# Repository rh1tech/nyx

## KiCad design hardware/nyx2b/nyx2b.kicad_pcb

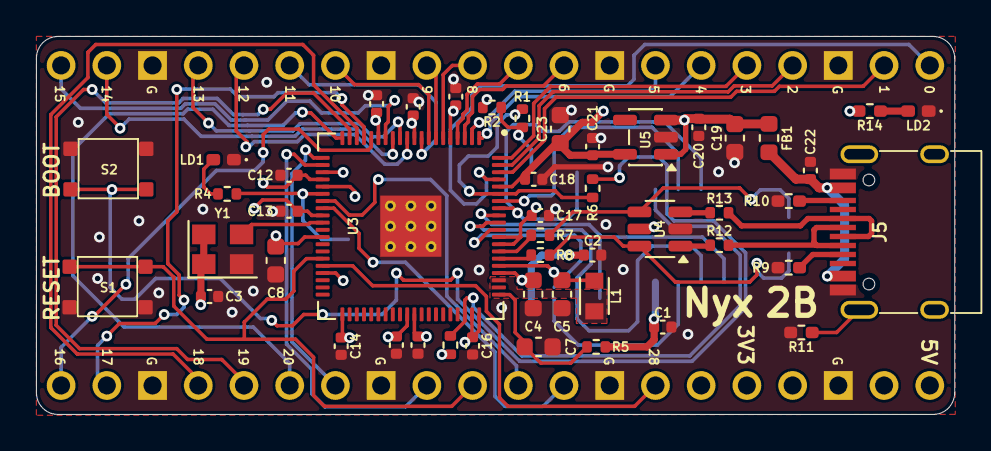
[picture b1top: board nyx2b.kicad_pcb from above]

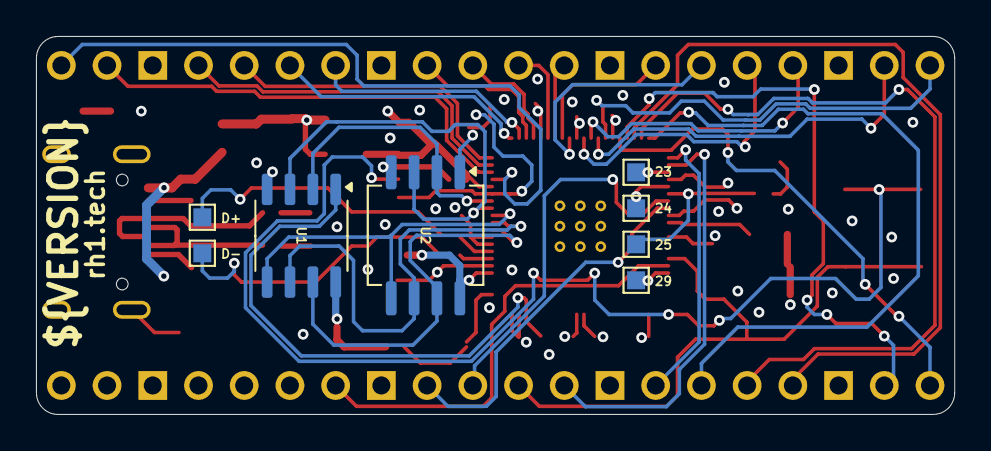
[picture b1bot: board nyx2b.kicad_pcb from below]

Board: 4 copper layers, 51.0 x 21.0 mm, 54 parts (4 on the bottom side), 61 nets.

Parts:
C1, C2, C3, C6, C9, C10, C11, C12, C13, C14, C15, C16, C17, C18, C20, C21, C22: 100n; Capacitor (0402, S)
C4, C5, C7, C8: 4.7u; Capacitor (0603, S)
C19, C23: 10u; Capacitor (0603, S)
FB1: 330R; L_0603_1608Metric
J1: CON_PICO_21-40
J2: CON_PICO_1-20
J3: Test Points (1mm x 5)
J4: Test Points (1mm x 2)
J5: USB4215-03-A; USB Type C
L1: 3.3u; IND_LQH2MCN100K02L
LD1: Blue; LED (0402)
LD2: Green; LED (0402)
R1: 0R; Resistor (0402, S)
R2, R3: 10K; Resistor (0402, S)
R4, R6: 1K; Resistor (0402, S)
R5: 33; Resistor (0402, S)
R7, R8: 27; Resistor (0402, S)
R9, R10: 5.1K; Resistor (0402)
R11: 1M; Resistor (0402)
R12, R13: 22R; Resistor (0402, S)
R14: 1K; Resistor (0402)
S1: Reset; Button (SMD, 3x3mm, 1-1)
S2: Boot; Button (SMD, 3x3mm, 1-1)
U1: ESP-PSRAM32; SO-8
U2: W25Q128JVS; SOIC-8
U3: RP2350_80QFN; RP2350-QFN-80-1EP_10x10_P0.4mm_EP3.4x3.4mm_ThermalVias
U4: USBLC6-2SC6; SOT-23-6
U5: ME6211C33M5; SOT-23-5
Y1: ASE-12MHz; Crystal (3225, active)

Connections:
+1V1: C5.1, C6.1, C8.1, C9.1, L1.1, U3.10 (DVDD), U3.32 (DVDD), U3.51 (DVDD), U3.65 (VREG_FB)
+3V3: C1.1, C2.1, C3.1, C4.1, C10.1, C11.1, C12.1, C13.1, C14.1, C15.1, C16.1, C17.1, C18.1, C21.1, C23.1, J1.36, R2.1, R3.2, R5.1, R14.2, U1.8 (VCC), U2.8 (VCC), U3.5 (IOVDD), U3.15 (IOVDD), U3.24 (IOVDD), U3.29 (IOVDD), U3.41 (IOVDD), U3.50 (IOVDD), U3.59 (ADC_AVDD), U3.60 (IOVDD), U3.64 (VREG_VIN), U3.68 (USB_OTP_VDD), U3.69 (QSPI_IOVDD), U3.76 (IOVDD), U5.5 (V_{OUT}), Y1.1 (EN), Y1.4 (Vdd)
/D+: J4.1, R7.1, U4.4 (I/O2)
/D-: J4.2, R8.1, U4.6 (I/O1)
/GPIO0: J2.1, U3.77 (GPIO0)
/GPIO1: J2.2, U3.78 (GPIO1)
/GPIO2: J2.4, U3.79 (GPIO2)
/GPIO3: J2.5, U3.80 (GPIO3)
/GPIO4: J2.6, U3.1 (GPIO4)
/GPIO5: J2.7, U3.2 (GPIO5)
/GPIO6: J2.9, U3.3 (GPIO6)
/GPIO7: J2.10, U3.4 (GPIO7)
/GPIO8: J2.11, U3.6 (GPIO8)
/GPIO9: J2.12, U3.7 (GPIO9)
/GPIO10: J2.14, U3.8 (GPIO10)
/GPIO11: J2.15, U3.9 (GPIO11)
/GPIO12: J2.16, U3.11 (GPIO12)
/GPIO13: J2.17, U3.12 (GPIO13)
/GPIO14: J2.19, U3.13 (GPIO14)
/GPIO15: J2.20, U3.14 (GPIO15)
/GPIO16: J1.21, U3.16 (GPIO16)
/GPIO17: J1.22, U3.17 (GPIO17)
/GPIO18: J1.24, U3.18 (GPIO18)
/GPIO19: J1.25, U3.19 (GPIO19)
/GPIO20: J1.26, U3.20 (GPIO20)
/GPIO21: J1.27, U3.21 (GPIO21)
/GPIO22: J1.29, U3.22 (GPIO22)
/GPIO23: J3.1, U3.23 (GPIO23)
/GPIO24: J3.2, U3.25 (GPIO24)
/GPIO26: J1.31, U3.27 (GPIO26)
/GPIO27: J1.32, U3.28 (GPIO27)
/GPIO28: J1.34, U3.36 (GPIO28)
/GPIO29: J3.4, U3.37 (GPIO29)
/GPIO47: R3.1, U1.1 (~CE), U3.58 (GPIO47_ADC7)
/Power/VBUS_IN: C22.1, FB1.2, J5.2 (VBUS), J5.11 (VBUS)
/RP2350B/FLASH_SS: R1.2, R2.2, U2.1 (~CS)
/RP2350B/QSPI_SCLK: U1.6 (SCLK), U2.6 (CLK), U3.71 (QSPI_SCLK)
/RP2350B/QSPI_SD0: U1.5 (SI/SIO), U2.5 (DI(IO0)), U3.72 (QSPI_SD0)
/RP2350B/QSPI_SD1: U1.2 (SO/SIO), U2.2 (DO(IO1)), U3.74 (QSPI_SD1)
/RP2350B/QSPI_SD2: U1.3 (SIO2), U2.3 (IO2), U3.73 (QSPI_SD2)
/RP2350B/QSPI_SD3: U1.7 (SIO3), U2.7 (IO3), U3.70 (QSPI_SD3)
/RP2350B/QSPI_SS: R1.1, R6.1, U3.75 (QSPI_SS)
/RP2350B/VREG_AVDD: C7.1, R5.2, U3.61 (VREG_AVDD)
/RP2350B/VREG_LX: L1.2, U3.63 (VREG_LX)
/RP2350B/XIN: U3.30 (XIN), Y1.3 (OUT)
/RP2350B/~USB_BOOT: R6.2, S2.2
/RUN: J1.30, S1.1, U3.35 (RUN)
GND: C1.2, C2.2, C3.2, C4.2, C5.2, C6.2, C7.2, C8.2, C9.2, C10.2, C11.2, C12.2, C13.2, C14.2, C15.2, C16.2, C17.2, C18.2, C19.1, C20.1, C21.2, C22.2, C23.2, J1.23, J1.28, J1.33, J1.38, J2.3, J2.8, J2.13, J2.18, J5.1 (GND), J5.12 (GND), LD1.1 (K), LD2.1 (K), R9.1, R10.1, R11.2, S1.2, S2.1, U1.4 (VSS), U2.4 (GND), U3.62 (VREG_PGND), U3.81 (GND), U4.2 (GND), U5.2 (V_{SS}), Y1.2 (GND)
GPIO25: J3.3, R4.2, U3.26 (GPIO25)
unnamed: J5.4 (CC1), R9.2
unnamed: J5.10 (CC2), R10.2
unnamed: J5.5 (DN2), J5.7 (DN1), R12.2
unnamed: J5.6 (DP1), J5.8 (DP2), R13.2
unnamed: J5.13 (SHIELD), R11.1
unnamed: LD1.2 (A), R4.1
unnamed: LD2.2 (A), R14.1
unnamed: R12.1, U4.1 (I/O1)
unnamed: R13.1, U4.3 (I/O2)
unnamed: R8.2, U3.66 (USB_DM)
unnamed: R7.2, U3.67 (USB_DP)
VBUS: C19.2, C20.2, FB1.1, J1.40, U4.5 (VBUS), U5.1 (V_{IN}), U5.3 (CE)

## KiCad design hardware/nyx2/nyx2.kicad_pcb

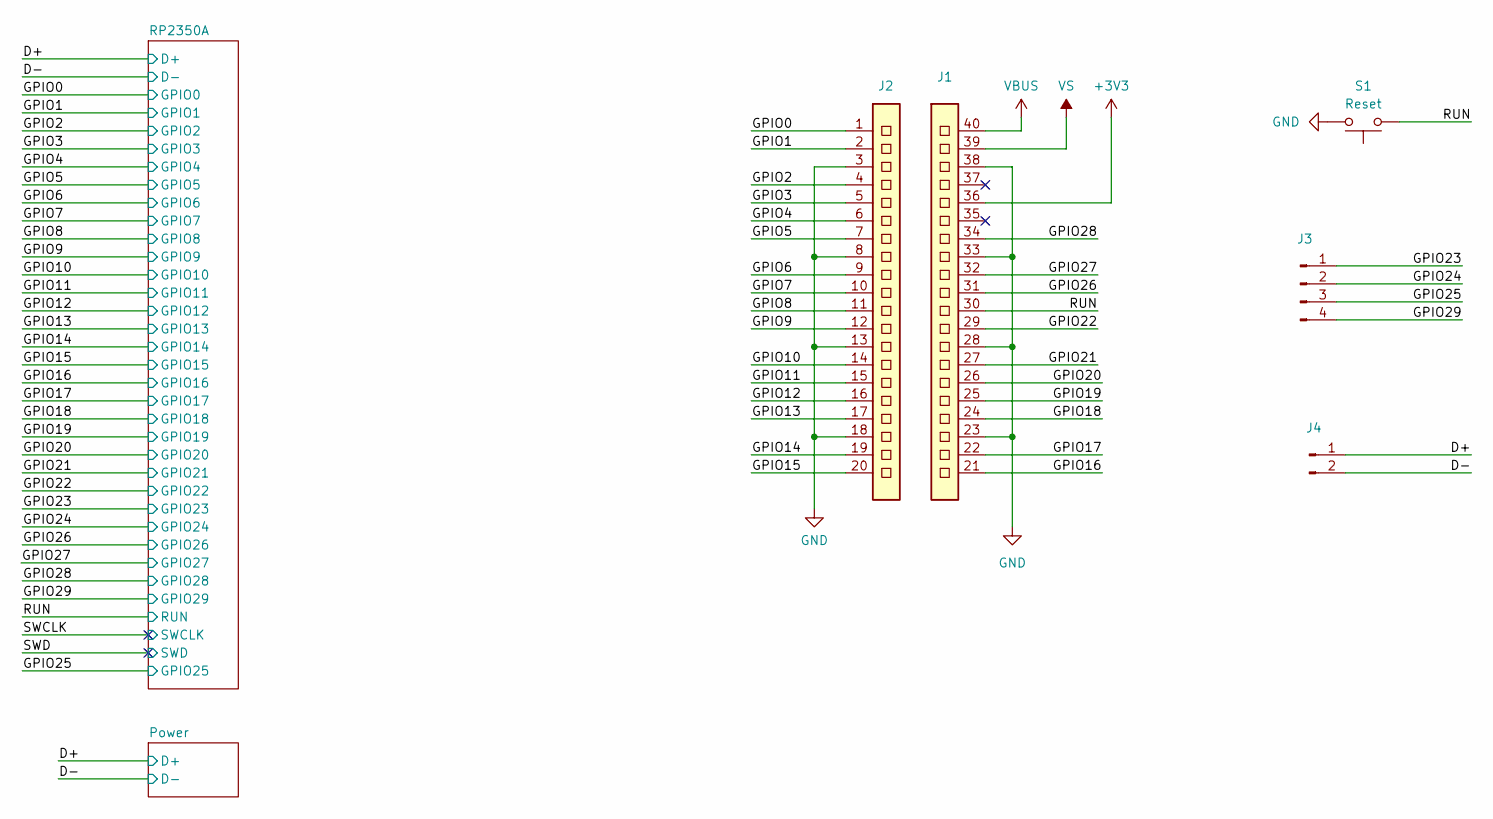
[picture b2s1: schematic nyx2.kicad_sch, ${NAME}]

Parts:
J1: CON_PICO_21-40
J2: CON_PICO_1-20
J3: Test Points (1mm x 5)
J4: Test Points (1mm x 2)
S1: Reset; Button (SMD, 3x3mm, 1-1)

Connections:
+3V3: J1.36; also elsewhere on the board
/D+: J4.1; also elsewhere on the board
/D-: J4.2; also elsewhere on the board
/GPIO0: J2.1; also elsewhere on the board
/GPIO1: J2.2; also elsewhere on the board
/GPIO2: J2.4; also elsewhere on the board
/GPIO3: J2.5; also elsewhere on the board
/GPIO4: J2.6; also elsewhere on the board
/GPIO5: J2.7; also elsewhere on the board
/GPIO6: J2.9; also elsewhere on the board
/GPIO7: J2.10; also elsewhere on the board
/GPIO8: J2.11; also elsewhere on the board
/GPIO9: J2.12; also elsewhere on the board
/GPIO10: J2.14; also elsewhere on the board
/GPIO11: J2.15; also elsewhere on the board
/GPIO12: J2.16; also elsewhere on the board
/GPIO13: J2.17; also elsewhere on the board
/GPIO14: J2.19; also elsewhere on the board
/GPIO15: J2.20; also elsewhere on the board
/GPIO16: J1.21; also elsewhere on the board
/GPIO17: J1.22; also elsewhere on the board
/GPIO18: J1.24; also elsewhere on the board
/GPIO19: J1.25; also elsewhere on the board
/GPIO20: J1.26; also elsewhere on the board
/GPIO21: J1.27; also elsewhere on the board
/GPIO22: J1.29; also elsewhere on the board
/GPIO23: J3.1; also elsewhere on the board
/GPIO24: J3.2; also elsewhere on the board
/GPIO26: J1.31; also elsewhere on the board
/GPIO27: J1.32; also elsewhere on the board
/GPIO28: J1.34; also elsewhere on the board
/GPIO29: J3.4; also elsewhere on the board
/RUN: J1.30, S1.1; also elsewhere on the board
GND: J1.23, J1.28, J1.33, J1.38, J2.3, J2.8, J2.13, J2.18, S1.2; also elsewhere on the board
GPIO25: J3.3; also elsewhere on the board
VBUS: J1.40; also elsewhere on the board
VS: J1.39

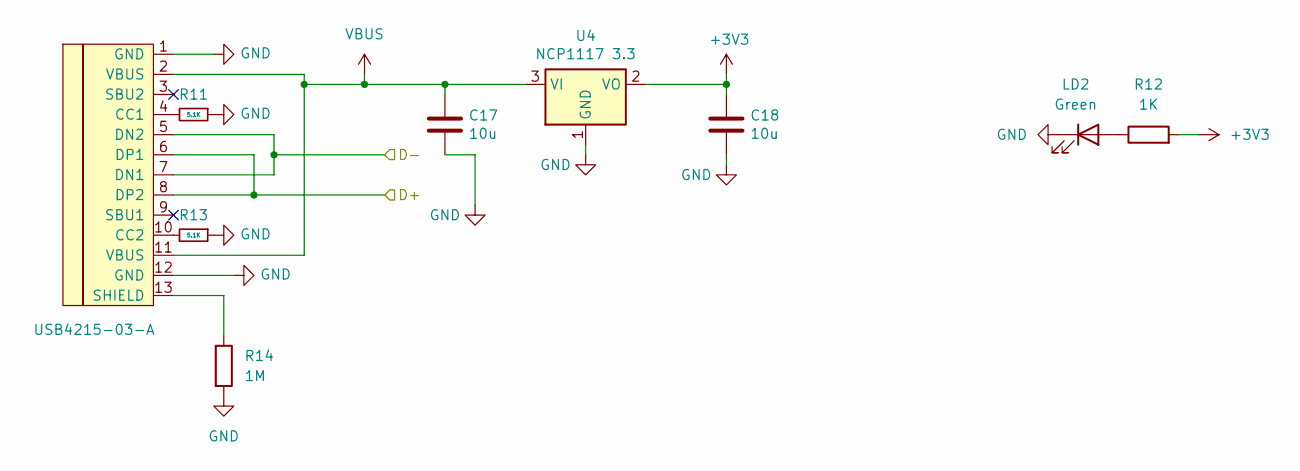
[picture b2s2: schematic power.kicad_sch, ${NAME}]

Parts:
C17, C18: 10u; Capacitor (0805)
J5: USB4215-03-A; USB Type C
LD2: Green; LED (0402)
R11, R13: 5.1K; Resistor (0402)
R12: 1K; Resistor (0402)
R14: 1M; Resistor (0402)
U4: NCP1117 3.3; SOT-223

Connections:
+3V3: C18.1, R12.2, U4.2 (VO); also elsewhere on the board
/D+: J5.6 (DP1), J5.8 (DP2); also elsewhere on the board
/D-: J5.5 (DN2), J5.7 (DN1); also elsewhere on the board
GND: C17.2, C18.2, J5.1 (GND), J5.12 (GND), LD2.1 (K), R11.1, R13.1, R14.2, U4.1 (GND); also elsewhere on the board
unnamed: J5.4 (CC1), R11.2
unnamed: J5.10 (CC2), R13.2
unnamed: J5.13 (SHIELD), R14.1
unnamed: LD2.2 (A), R12.1
VBUS: C17.1, J5.2 (VBUS), J5.11 (VBUS), U4.3 (VI); also elsewhere on the board

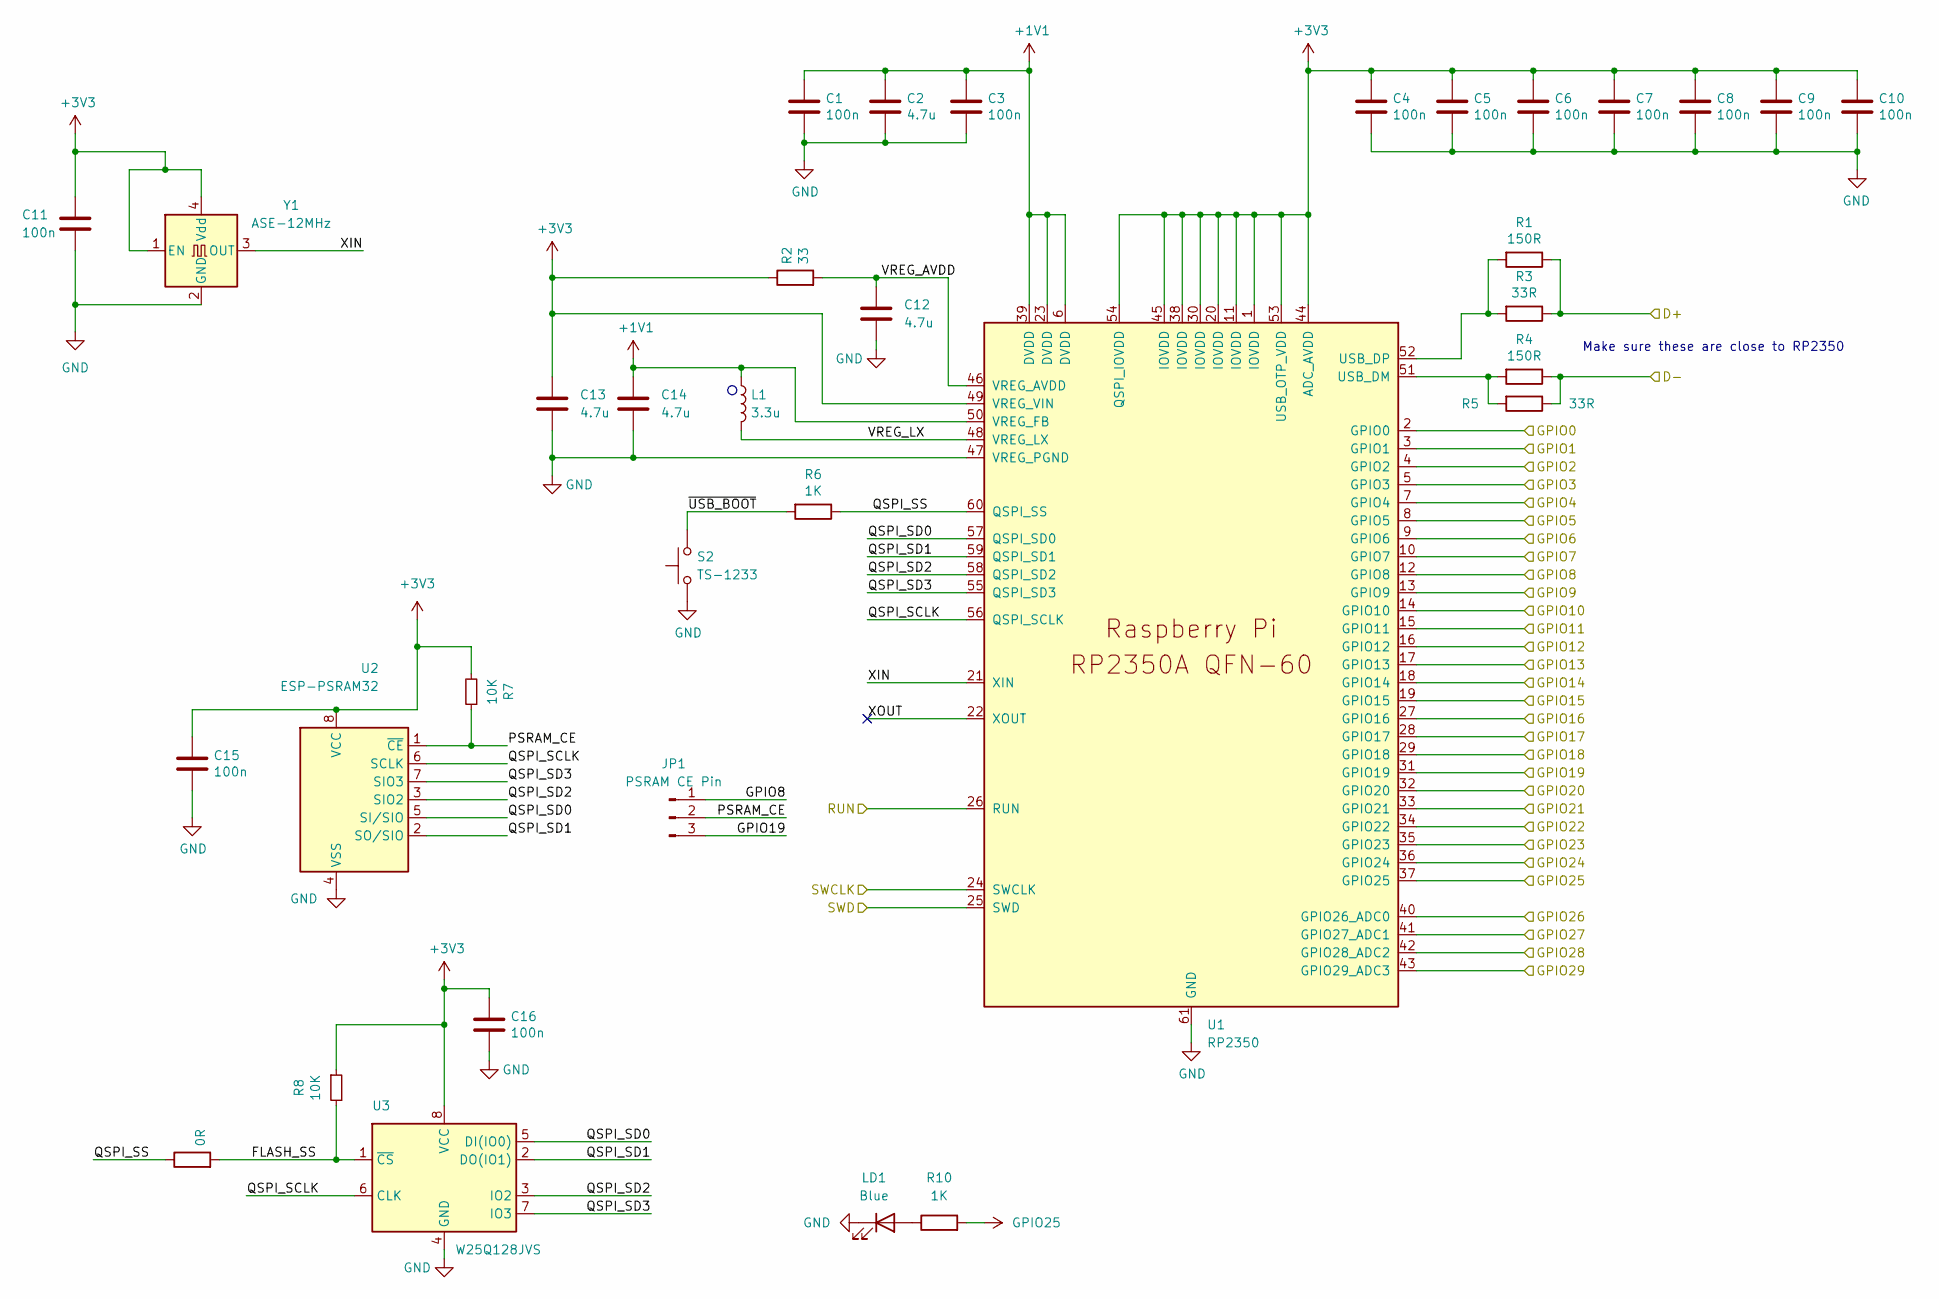
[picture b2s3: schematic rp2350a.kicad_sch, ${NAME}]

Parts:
C1, C3, C4, C5, C6, C7, C8, C9, C10, C11, C15, C16: 100n; Capacitor (0402)
C2, C12, C13, C14: 4.7u; Capacitor (0805)
JP1: PSRAM CE Pin; Jumper (solder, 3 pins)
L1: 3.3u; IND_LQH2MCN100K02L
LD1: Blue; LED (0402)
R1, R4: 150R; Resistor (0402)
R2: 33; Resistor (0402)
R3, R5: 33R; Resistor (0402)
R6, R10: 1K; Resistor (0402)
R7, R8: 10K; Resistor (0402)
R9: 0R; Resistor (0402)
S2: TS-1233; Button (SMD, 3x3mm, 1-1)
U1: RP2350; QFN 60 (RP2350A)
U2: ESP-PSRAM32; SO-8
U3: W25Q128JVS; SOIC-8
Y1: ASE-12MHz; Crystal (3225, active)

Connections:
+1V1: C1.1, C2.1, C3.1, C14.1, L1.1, U1.6 (DVDD), U1.23 (DVDD), U1.39 (DVDD), U1.50 (VREG_FB)
+3V3: C4.1, C5.1, C6.1, C7.1, C8.1, C9.1, C10.1, C11.1, C13.1, C15.1, C16.1, R2.1, R7.2, R8.1, U1.1 (IOVDD), U1.11 (IOVDD), U1.20 (IOVDD), U1.30 (IOVDD), U1.38 (IOVDD), U1.44 (ADC_AVDD), U1.45 (IOVDD), U1.49 (VREG_VIN), U1.53 (USB_OTP_VDD), U1.54 (QSPI_IOVDD), U2.8 (VCC), U3.8 (VCC), Y1.1 (EN), Y1.4 (Vdd); also elsewhere on the board
/D+: R1.1, R3.1; also elsewhere on the board
/D-: R4.1, R5.1; also elsewhere on the board
/GPIO0: U1.2 (GPIO0); also elsewhere on the board
/GPIO1: U1.3 (GPIO1); also elsewhere on the board
/GPIO2: U1.4 (GPIO2); also elsewhere on the board
/GPIO3: U1.5 (GPIO3); also elsewhere on the board
/GPIO4: U1.7 (GPIO4); also elsewhere on the board
/GPIO5: U1.8 (GPIO5); also elsewhere on the board
/GPIO6: U1.9 (GPIO6); also elsewhere on the board
/GPIO7: U1.10 (GPIO7); also elsewhere on the board
/GPIO8: JP1.1, U1.12 (GPIO8); also elsewhere on the board
/GPIO9: U1.13 (GPIO9); also elsewhere on the board
/GPIO10: U1.14 (GPIO10); also elsewhere on the board
/GPIO11: U1.15 (GPIO11); also elsewhere on the board
/GPIO12: U1.16 (GPIO12); also elsewhere on the board
/GPIO13: U1.17 (GPIO13); also elsewhere on the board
/GPIO14: U1.18 (GPIO14); also elsewhere on the board
/GPIO15: U1.19 (GPIO15); also elsewhere on the board
/GPIO16: U1.27 (GPIO16); also elsewhere on the board
/GPIO17: U1.28 (GPIO17); also elsewhere on the board
/GPIO18: U1.29 (GPIO18); also elsewhere on the board
/GPIO19: JP1.3, U1.31 (GPIO19); also elsewhere on the board
/GPIO20: U1.32 (GPIO20); also elsewhere on the board
/GPIO21: U1.33 (GPIO21); also elsewhere on the board
/GPIO22: U1.34 (GPIO22); also elsewhere on the board
/GPIO23: U1.35 (GPIO23); also elsewhere on the board
/GPIO24: U1.36 (GPIO24); also elsewhere on the board
/GPIO26: U1.40 (GPIO26_ADC0); also elsewhere on the board
/GPIO27: U1.41 (GPIO27_ADC1); also elsewhere on the board
/GPIO28: U1.42 (GPIO28_ADC2); also elsewhere on the board
/GPIO29: U1.43 (GPIO29_ADC3); also elsewhere on the board
/RP2350A/FLASH_SS: R8.2, R9.2, U3.1 (~CS)
/RP2350A/PSRAM_CE: JP1.2, R7.1, U2.1 (~CE)
/RP2350A/QSPI_SCLK: U1.56 (QSPI_SCLK), U2.6 (SCLK), U3.6 (CLK)
/RP2350A/QSPI_SD0: U1.57 (QSPI_SD0), U2.5 (SI/SIO), U3.5 (DI(IO0))
/RP2350A/QSPI_SD1: U1.59 (QSPI_SD1), U2.2 (SO/SIO), U3.2 (DO(IO1))
/RP2350A/QSPI_SD2: U1.58 (QSPI_SD2), U2.3 (SIO2), U3.3 (IO2)
/RP2350A/QSPI_SD3: U1.55 (QSPI_SD3), U2.7 (SIO3), U3.7 (IO3)
/RP2350A/QSPI_SS: R6.1, R9.1, U1.60 (QSPI_SS)
/RP2350A/VREG_AVDD: C12.1, R2.2, U1.46 (VREG_AVDD)
/RP2350A/VREG_LX: L1.2, U1.48 (VREG_LX)
/RP2350A/XIN: U1.21 (XIN), Y1.3 (OUT)
/RP2350A/XOUT: U1.22 (XOUT)
/RP2350A/~USB_BOOT: R6.2, S2.2
/RUN: U1.26 (RUN); also elsewhere on the board
/SWCLK: U1.24 (SWCLK)
/SWD: U1.25 (SWD)
GND: C1.2, C2.2, C3.2, C4.2, C5.2, C6.2, C7.2, C8.2, C9.2, C10.2, C11.2, C12.2, C13.2, C14.2, C15.2, C16.2, LD1.1 (K), S2.1, U1.47 (VREG_PGND), U1.61 (GND), U2.4 (VSS), U3.4 (GND), Y1.2 (GND); also elsewhere on the board
GPIO25: R10.2, U1.37 (GPIO25); also elsewhere on the board
unnamed: LD1.2 (A), R10.1
unnamed: R4.2, R5.2, U1.51 (USB_DM)
unnamed: R1.2, R3.2, U1.52 (USB_DP)

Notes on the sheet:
Make sure these are close to RP2350

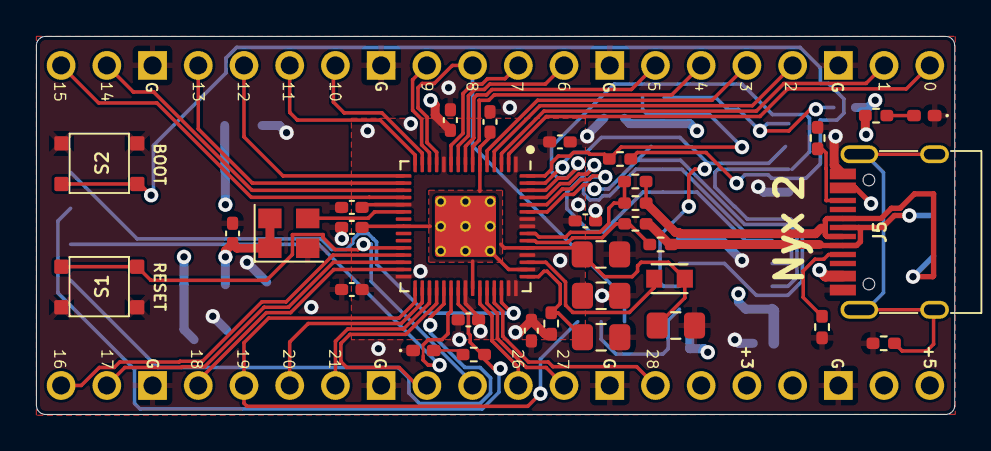
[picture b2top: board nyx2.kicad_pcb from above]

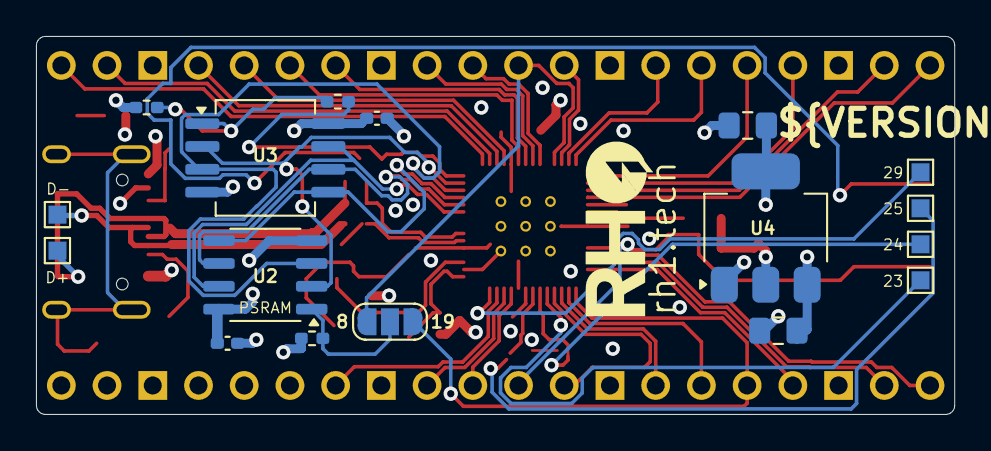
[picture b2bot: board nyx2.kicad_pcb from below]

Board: 4 copper layers, 51.0 x 21.0 mm, 48 parts (13 on the bottom side), 56 nets.

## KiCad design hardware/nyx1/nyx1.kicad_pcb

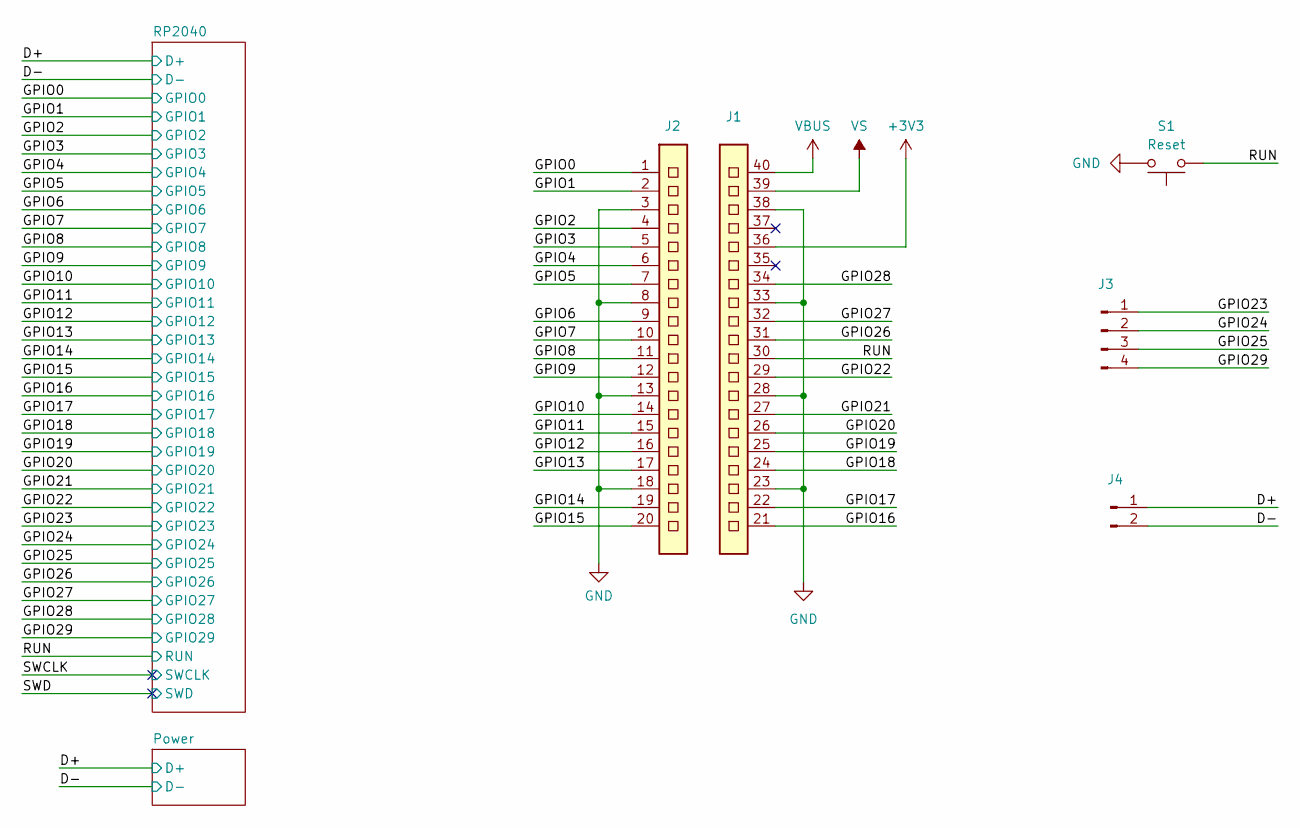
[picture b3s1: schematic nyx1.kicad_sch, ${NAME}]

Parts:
J1: CON_PICO_21-40
J2: CON_PICO_1-20
J3: Test Points (1mm x 5)
J4: Test Points (1mm x 2)
S1: Reset; Button (SMD, 3x3mm, 1-1)

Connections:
+3V3: J1.36; also elsewhere on the board
/D+: J4.1; also elsewhere on the board
/D-: J4.2; also elsewhere on the board
/GPIO0: J2.1; also elsewhere on the board
/GPIO1: J2.2; also elsewhere on the board
/GPIO2: J2.4; also elsewhere on the board
/GPIO3: J2.5; also elsewhere on the board
/GPIO4: J2.6; also elsewhere on the board
/GPIO5: J2.7; also elsewhere on the board
/GPIO6: J2.9; also elsewhere on the board
/GPIO7: J2.10; also elsewhere on the board
/GPIO8: J2.11; also elsewhere on the board
/GPIO9: J2.12; also elsewhere on the board
/GPIO10: J2.14; also elsewhere on the board
/GPIO11: J2.15; also elsewhere on the board
/GPIO12: J2.16; also elsewhere on the board
/GPIO13: J2.17; also elsewhere on the board
/GPIO14: J2.19; also elsewhere on the board
/GPIO15: J2.20; also elsewhere on the board
/GPIO16: J1.21; also elsewhere on the board
/GPIO17: J1.22; also elsewhere on the board
/GPIO18: J1.24; also elsewhere on the board
/GPIO19: J1.25; also elsewhere on the board
/GPIO20: J1.26; also elsewhere on the board
/GPIO21: J1.27; also elsewhere on the board
/GPIO22: J1.29; also elsewhere on the board
/GPIO23: J3.1; also elsewhere on the board
/GPIO24: J3.2; also elsewhere on the board
/GPIO25: J3.3; also elsewhere on the board
/GPIO26: J1.31; also elsewhere on the board
/GPIO27: J1.32; also elsewhere on the board
/GPIO28: J1.34; also elsewhere on the board
/GPIO29: J3.4; also elsewhere on the board
/RUN: J1.30, S1.1; also elsewhere on the board
GND: J1.23, J1.28, J1.33, J1.38, J2.3, J2.8, J2.13, J2.18, S1.2; also elsewhere on the board
VBUS: J1.40; also elsewhere on the board
VS: J1.39

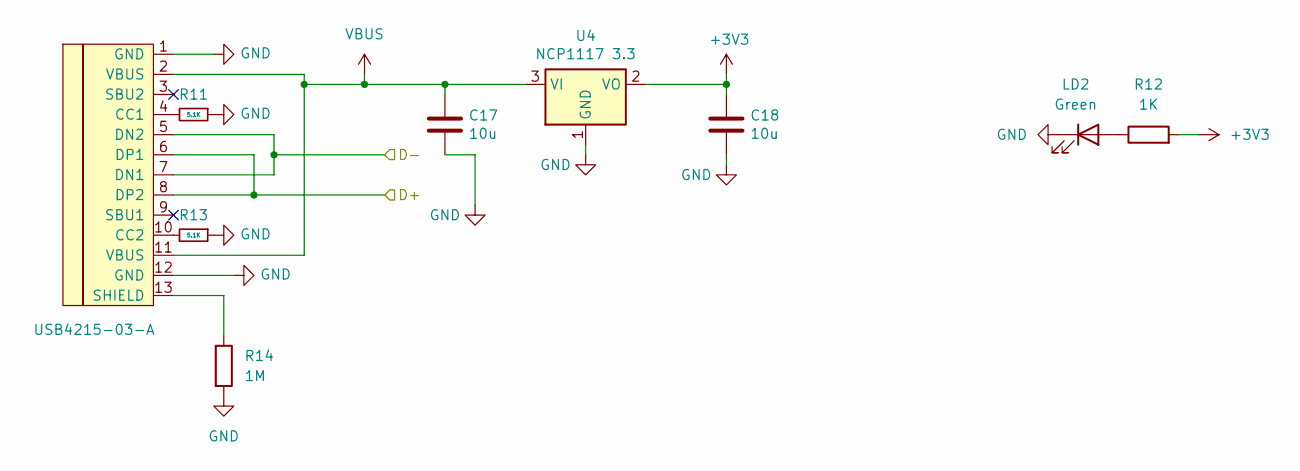
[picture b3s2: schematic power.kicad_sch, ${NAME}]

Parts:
C17, C18: 10u; Capacitor (0603)
J5: USB4215-03-A; USB Type C
LD2: Green; LED (0402)
R11, R13: 5.1K; Resistor (0402)
R12: 1K; Resistor (0402)
R14: 1M; Resistor (0402)
U4: NCP1117 3.3; SOT-223

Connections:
+3V3: C18.1, R12.2, U4.2 (VO); also elsewhere on the board
/D+: J5.6 (DP1), J5.8 (DP2); also elsewhere on the board
/D-: J5.5 (DN2), J5.7 (DN1); also elsewhere on the board
GND: C17.2, C18.2, J5.1 (GND), J5.12 (GND), LD2.1 (K), R11.1, R13.1, R14.2, U4.1 (GND); also elsewhere on the board
unnamed: J5.4 (CC1), R11.2
unnamed: J5.10 (CC2), R13.2
unnamed: J5.13 (SHIELD), R14.1
unnamed: LD2.2 (A), R12.1
VBUS: C17.1, J5.2 (VBUS), J5.11 (VBUS), U4.3 (VI); also elsewhere on the board

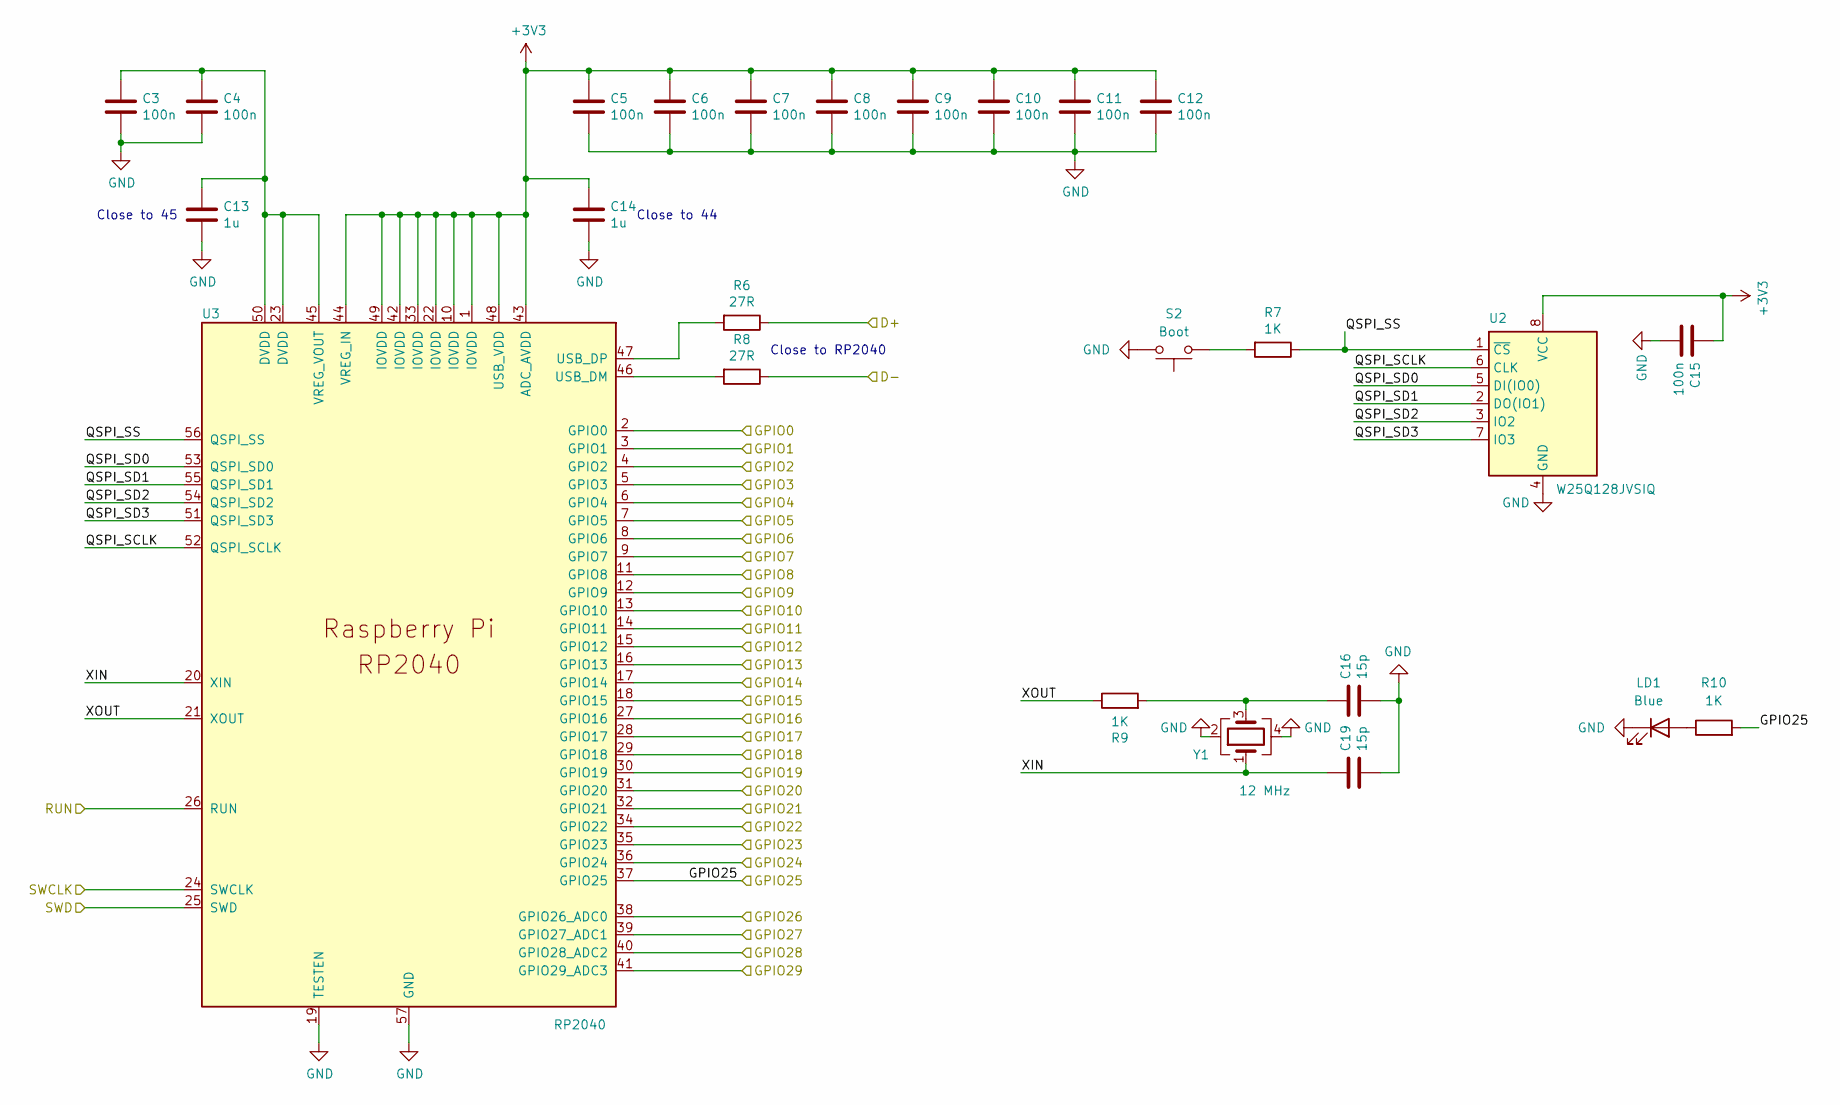
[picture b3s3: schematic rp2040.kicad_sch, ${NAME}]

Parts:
C3, C4, C5, C6, C7, C8, C9, C10, C11, C12, C15: 100n; Capacitor (0402)
C13, C14: 1u; Capacitor (0603)
C16, C19: 15p; Capacitor (0402)
LD1: Blue; LED (0402)
R6, R8: 27R; Resistor (0402)
R7, R9, R10: 1K; Resistor (0402)
S2: Boot; Button (SMD, 3x3mm, 1-1)
U2: W25Q128JVSIQ; SOIC-8
U3: RP2040; QFN 56
Y1: 12 MHz; Crystal (3225)

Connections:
+3V3: C5.1, C6.1, C7.1, C8.1, C9.1, C10.1, C11.1, C12.1, C14.1, C15.1, U2.8 (VCC), U3.1 (IOVDD), U3.10 (IOVDD), U3.22 (IOVDD), U3.33 (IOVDD), U3.42 (IOVDD), U3.43 (ADC_AVDD), U3.44 (VREG_IN), U3.48 (USB_VDD), U3.49 (IOVDD); also elsewhere on the board
/D+: R6.1; also elsewhere on the board
/D-: R8.1; also elsewhere on the board
/GPIO0: U3.2 (GPIO0); also elsewhere on the board
/GPIO1: U3.3 (GPIO1); also elsewhere on the board
/GPIO2: U3.4 (GPIO2); also elsewhere on the board
/GPIO3: U3.5 (GPIO3); also elsewhere on the board
/GPIO4: U3.6 (GPIO4); also elsewhere on the board
/GPIO5: U3.7 (GPIO5); also elsewhere on the board
/GPIO6: U3.8 (GPIO6); also elsewhere on the board
/GPIO7: U3.9 (GPIO7); also elsewhere on the board
/GPIO8: U3.11 (GPIO8); also elsewhere on the board
/GPIO9: U3.12 (GPIO9); also elsewhere on the board
/GPIO10: U3.13 (GPIO10); also elsewhere on the board
/GPIO11: U3.14 (GPIO11); also elsewhere on the board
/GPIO12: U3.15 (GPIO12); also elsewhere on the board
/GPIO13: U3.16 (GPIO13); also elsewhere on the board
/GPIO14: U3.17 (GPIO14); also elsewhere on the board
/GPIO15: U3.18 (GPIO15); also elsewhere on the board
/GPIO16: U3.27 (GPIO16); also elsewhere on the board
/GPIO17: U3.28 (GPIO17); also elsewhere on the board
/GPIO18: U3.29 (GPIO18); also elsewhere on the board
/GPIO19: U3.30 (GPIO19); also elsewhere on the board
/GPIO20: U3.31 (GPIO20); also elsewhere on the board
/GPIO21: U3.32 (GPIO21); also elsewhere on the board
/GPIO22: U3.34 (GPIO22); also elsewhere on the board
/GPIO23: U3.35 (GPIO23); also elsewhere on the board
/GPIO24: U3.36 (GPIO24); also elsewhere on the board
/GPIO25: R10.2, U3.37 (GPIO25); also elsewhere on the board
/GPIO26: U3.38 (GPIO26_ADC0); also elsewhere on the board
/GPIO27: U3.39 (GPIO27_ADC1); also elsewhere on the board
/GPIO28: U3.40 (GPIO28_ADC2); also elsewhere on the board
/GPIO29: U3.41 (GPIO29_ADC3); also elsewhere on the board
/RP2040/QSPI_SCLK: U2.6 (CLK), U3.52 (QSPI_SCLK)
/RP2040/QSPI_SD0: U2.5 (DI(IO0)), U3.53 (QSPI_SD0)
/RP2040/QSPI_SD1: U2.2 (DO(IO1)), U3.55 (QSPI_SD1)
/RP2040/QSPI_SD2: U2.3 (IO2), U3.54 (QSPI_SD2)
/RP2040/QSPI_SD3: U2.7 (IO3), U3.51 (QSPI_SD3)
/RP2040/QSPI_SS: R7.1, U2.1 (~CS), U3.56 (QSPI_SS)
/RP2040/XIN: C19.1, U3.20 (XIN), Y1.1
/RP2040/XOUT: R9.1, U3.21 (XOUT)
/RUN: U3.26 (RUN); also elsewhere on the board
/SWCLK: U3.24 (SWCLK)
/SWD: U3.25 (SWD)
GND: C3.2, C4.2, C5.2, C6.2, C7.2, C8.2, C9.2, C10.2, C11.2, C12.2, C13.2, C14.2, C15.2, C16.2, C19.2, LD1.1 (K), S2.2, U2.4 (GND), U3.19 (TESTEN), U3.57 (GND), Y1.2, Y1.4; also elsewhere on the board
unnamed: C16.1, R9.2, Y1.3
unnamed: LD1.2 (A), R10.1
unnamed: R7.2, S2.1
unnamed: R8.2, U3.46 (USB_DM)
unnamed: R6.2, U3.47 (USB_DP)
unnamed: C3.1, C4.1, C13.1, U3.23 (DVDD), U3.45 (VREG_VOUT), U3.50 (DVDD)

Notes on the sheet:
Close to 44
Close to RP2040
Close to 45

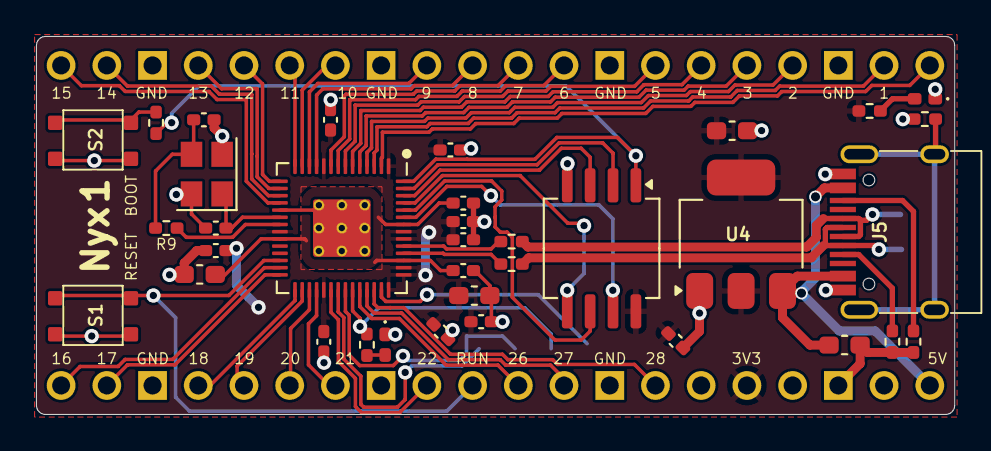
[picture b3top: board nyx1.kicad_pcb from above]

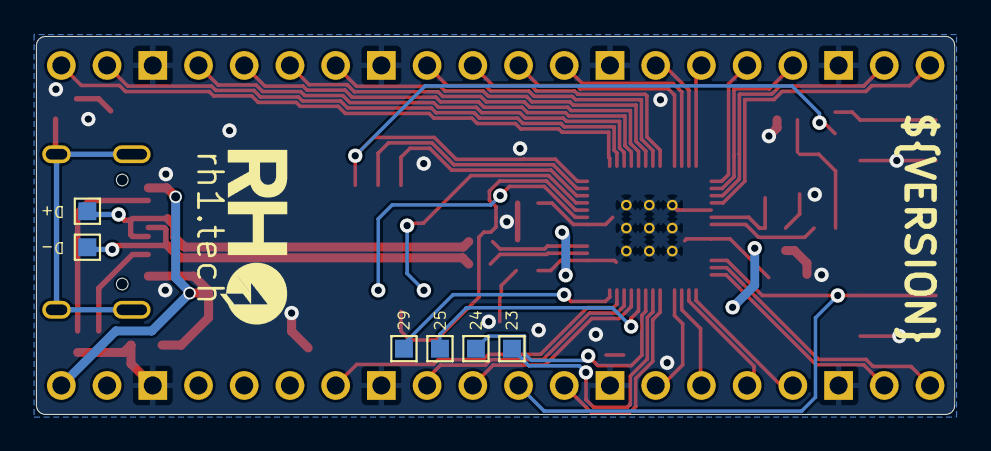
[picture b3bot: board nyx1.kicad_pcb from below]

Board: 2 copper layers, 51.0 x 21.0 mm, 39 parts (2 on the bottom side), 54 nets.

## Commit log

2025-06-23 Added license file
2025-08-02 Nyx 1 Added, cleanup
2025-08-02 Cleanup
2025-08-04 Nyx1 Release
2025-11-13 Nyx 2B released + repo cleanup
2025-11-14 Minor updates
